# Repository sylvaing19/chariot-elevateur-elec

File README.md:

# chariot-elevateur-elec
Robot's motherboard Eagle files

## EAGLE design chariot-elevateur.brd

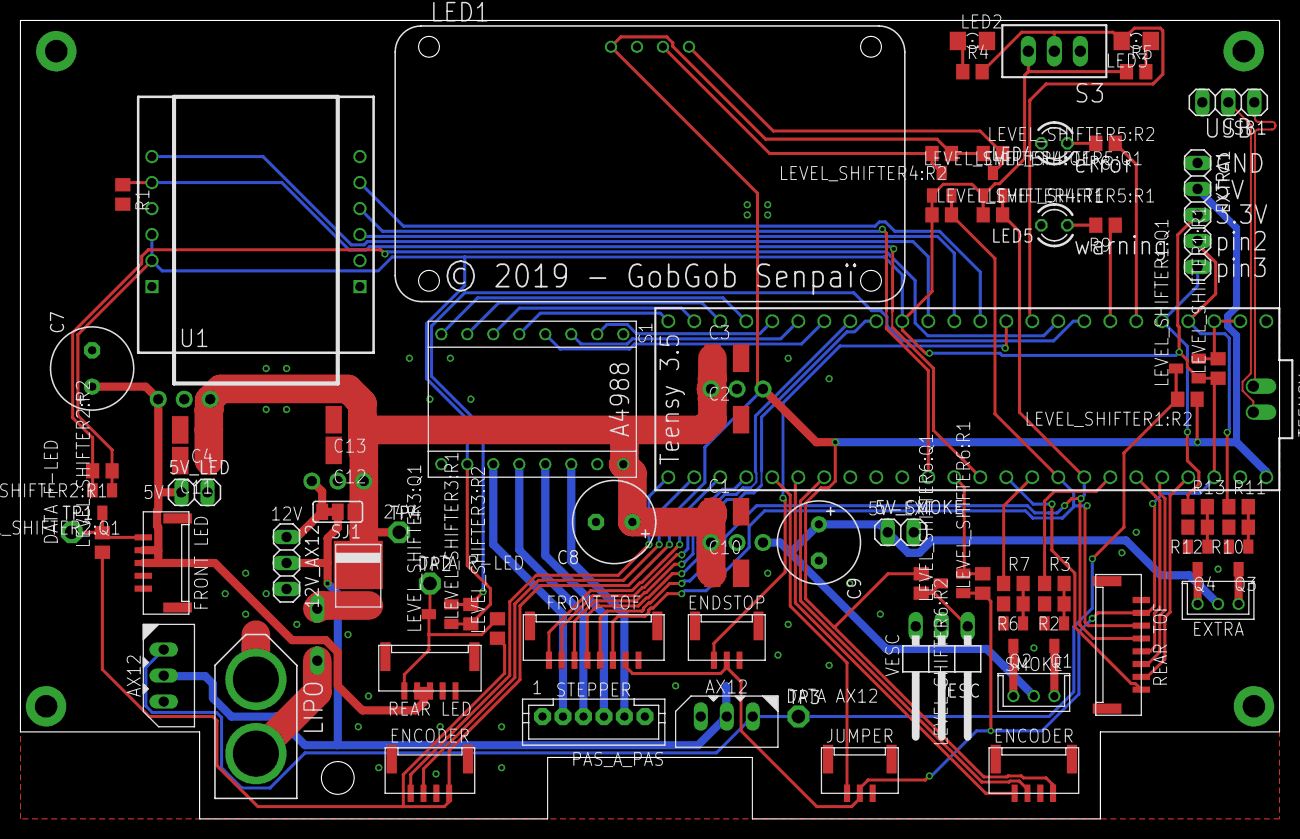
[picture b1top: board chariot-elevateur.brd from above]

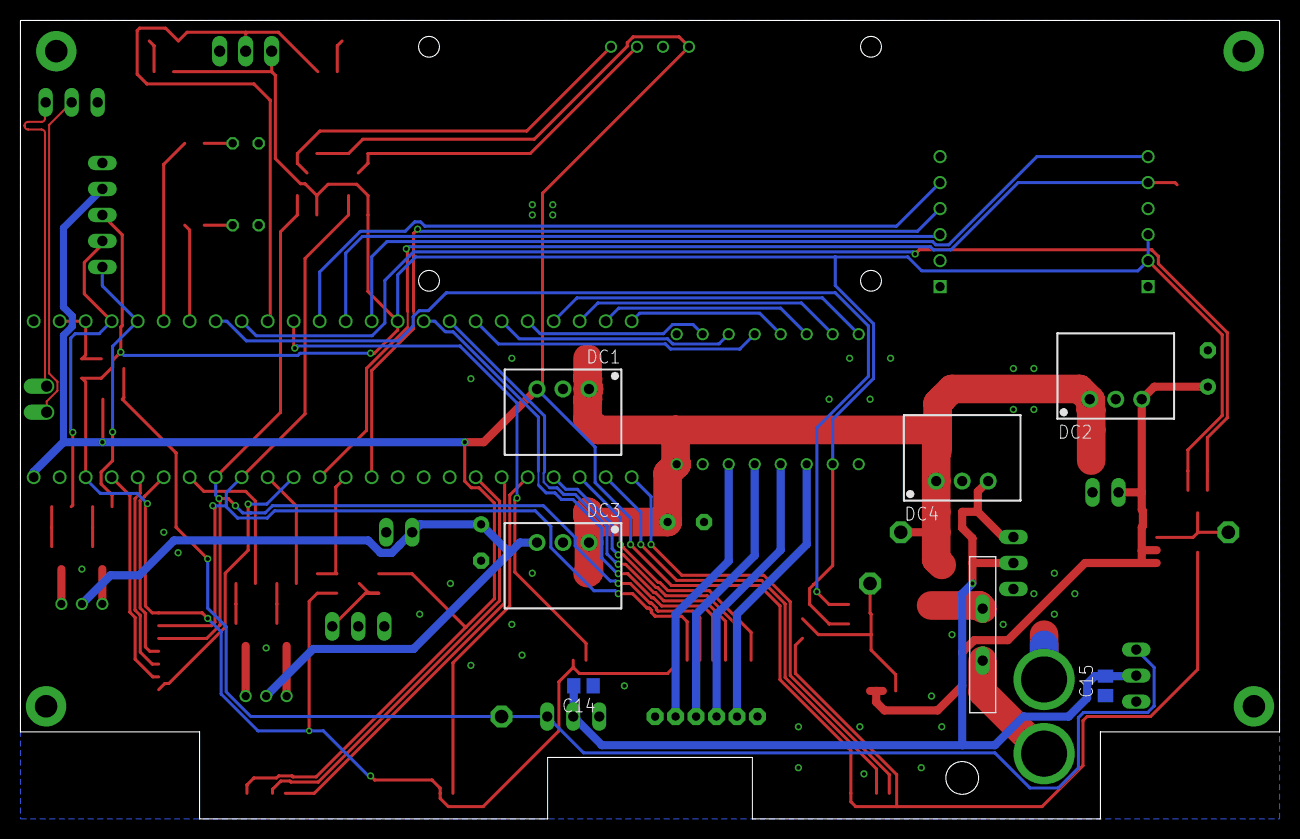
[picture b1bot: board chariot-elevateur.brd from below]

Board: 2 copper layers, 123.0 x 78.0 mm, 88 parts (7 on the bottom side), 73 nets.

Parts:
5V_LED, 5V_SMOKE: 1X02
12V_AX12: 1X03
AX12_AR, AX12_AV: DYNAMIXEL-1X03AX; DYNAMIXEL_AX_1X03
C1, C2, C3, C4, C10, C11, C12, C13: 10µF/50V; C1210
C7, C9: 220µF/25V; E3,5-8
C8: 100µF/50V; E3,5-8
C14, C15: 1µF; C0805
D1: DIODE_S15P45; TO-277A
DC1, DC2: TSR 1-2450; SIP3
DC3: TSR 2-2450; SIP3
DC4: TSR 2-24120; SIP3
ENCODEUR_DROIT: JST-04GH-V; GH-04-V
ENCODEUR_GAUCHE: JST-04GH-V; GH-04-V
ENDSTOP: JST-03; GH-03-V
EXTRA: DYNAMIXEL-1X03XL; DYNAMIXEL_XL_1X03
EXTRA1: 1X05
FUMIGENE: DYNAMIXEL-1X03XL; DYNAMIXEL_XL_1X03
JUMPER: JST-03; GH-03-V
LED1: ADAFRUIT_7-SEGMENT-LED; 0.56"LED_BACKPACK
LED2: blue; 1206
LED3: orange; 1206
LED4: red; LED3MM
LED5: orange; LED3MM
LEVEL_SHIFTER1:Q1, LEVEL_SHIFTER2:Q1, LEVEL_SHIFTER3:Q1, LEVEL_SHIFTER4:Q1, LEVEL_SHIFTER5:Q1, LEVEL_SHIFTER6:Q1: BSS138; SOT23
LEVEL_SHIFTER1:R1, LEVEL_SHIFTER1:R2, LEVEL_SHIFTER2:R1, LEVEL_SHIFTER2:R2, LEVEL_SHIFTER3:R1, LEVEL_SHIFTER3:R2, LEVEL_SHIFTER4:R1, LEVEL_SHIFTER4:R2, LEVEL_SHIFTER5:R1, LEVEL_SHIFTER5:R2, LEVEL_SHIFTER6:R1, LEVEL_SHIFTER6:R2: 10k; R0805
LIPO: XT-60
P1: RG500; 5MM
PAS_A_PAS: JST-PH6
PHARES_AR: JST-05; GH-05-V
PHARES_AV: JST-05; GH-05-V
Q1, Q2, Q3, Q4: DMN2056U; SOT23
R1, R2, R6, R10, R12: 10k; R0805
R3, R7, R11, R13: 100; R0805
R4, R5, R8, R9: 330; R0805
S1: A4988-BREAKOUT
S3: TL36PO; TL3XPO
SJ1: SJ_2
TEENSY: TEENSY_3.5_DIL+USB
TOF_AR: JST-08; GH-08-V
TOF_AV: JST-08; GH-08-V
TP1, TP2, TP3, TP4: PTR1PAD1-13; P1-13
U1: WIZ820IO; WIZ820
USB1: 1X03
VESC: 1X03/90

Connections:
+3V3: ENDSTOP.2, EXTRA1.3, JUMPER.2, LEVEL_SHIFTER1:Q1.1, LEVEL_SHIFTER1:R1.1, LEVEL_SHIFTER2:Q1.1, LEVEL_SHIFTER2:R1.1, LEVEL_SHIFTER3:Q1.1, LEVEL_SHIFTER3:R1.1, LEVEL_SHIFTER4:Q1.1, LEVEL_SHIFTER4:R1.1, LEVEL_SHIFTER5:Q1.1, LEVEL_SHIFTER5:R1.1, LEVEL_SHIFTER6:Q1.1, LEVEL_SHIFTER6:R1.1, R5.1, S1.VDD, S3.3, TEENSY.3.3V, TEENSY.3.3V3, TOF_AR.2, TOF_AV.2, U1.VIN1, U1.VIN2
+5V/1: DC1.3, ENCODEUR_DROIT.1, ENCODEUR_GAUCHE.1, EXTRA1.2, LED1.VCC, LEVEL_SHIFTER1:R2.1, LEVEL_SHIFTER2:R2.1, LEVEL_SHIFTER3:R2.1, LEVEL_SHIFTER4:R2.1, LEVEL_SHIFTER5:R2.1, LEVEL_SHIFTER6:R2.1, TEENSY.VIN
+5V/2: 5V_LED.1, C7.+, DC2.3, PHARES_AR.3, PHARES_AR.4, PHARES_AV.3, PHARES_AV.4
+5V/3: 5V_SMOKE.1, C9.+, DC3.3, EXTRA.VCC, FUMIGENE.VCC
+12V: 12V_AX12.2, AX12_AR.DYN_VCC, AX12_AV.DYN_VCC, C14.2, C15.2, SJ1.2
+24V: C1.1, C2.1, C3.1, C4.1, C8.+, C10.1, C11.1, C12.1, C13.1, D1.-, DC1.1, DC2.1, DC3.1, DC4.1, S1.VMOT, SJ1.1, TP4.TP
CHOOSE_COLOR: LED3.C, R4.2, S3.2, TEENSY.8
CMD_DEL_AR: LEVEL_SHIFTER3:Q1.2, LEVEL_SHIFTER3:R1.2, TEENSY.6
CMD_DEL_AR_5V: LEVEL_SHIFTER3:Q1.3, LEVEL_SHIFTER3:R2.2, PHARES_AR.5, TP2.TP
CMD_DEL_AV: LEVEL_SHIFTER2:Q1.2, LEVEL_SHIFTER2:R1.2, TEENSY.7
CMD_DEL_AV_5V: LEVEL_SHIFTER2:Q1.3, LEVEL_SHIFTER2:R2.2, PHARES_AV.5, TP1.TP
CMD_FUM_POMPE: R3.1, TEENSY.20/A6
CMD_FUM_RES: R7.1, TEENSY.17/A3
DEL_ERROR: R8.1, TEENSY.4
DEL_WARNING: R9.1, TEENSY.5
DIR: S1.DIR, TEENSY.29
ENC_D_A: ENCODEUR_DROIT.3, TEENSY.39/A20
ENC_D_B: ENCODEUR_DROIT.4, TEENSY.38/A19
ENC_G_A: ENCODEUR_GAUCHE.3, TEENSY.34/A15
ENC_G_B: ENCODEUR_GAUCHE.4, TEENSY.33/A14
ENDSTOP: ENDSTOP.3, TEENSY.9
ETH_MISO: TEENSY.12, U1.MISO
ETH_MOSI: TEENSY.11, U1.MOSI
ETH_RST: R1.1, TEENSY.15/A1, U1.RESET
ETH_SCLK: TEENSY.13, U1.SCLK
ETH_SS: TEENSY.10, U1.SS
EXTRA_GPIO_1: EXTRA1.4, R11.1, TEENSY.2
EXTRA_GPIO_2: EXTRA1.5, R13.1, TEENSY.3
EXTRA_POWER_SWITCH_1: EXTRA.GND, Q3.3
EXTRA_POWER_SWITCH_2: EXTRA.DATA, Q4.3
FUM_POMPE: FUMIGENE.GND, Q1.3
FUM_RES: FUMIGENE.DATA, Q2.3
GND: 5V_LED.2, 5V_SMOKE.2, 12V_AX12.3, AX12_AR.GND, AX12_AV.GND, C1.2, C2.2, C3.2, C4.2, C7.-, C8.-, C9.-, C10.2, C11.2, C12.2, C13.2, C14.1, C15.1, DC1.2, DC2.2, DC3.2, DC4.2, ENCODEUR_DROIT.2, ENCODEUR_GAUCHE.2, ENDSTOP.1, EXTRA1.1, JUMPER.1, LED1.GND, LED2.C, LED4.K, LED5.K, LIPO.(-), PHARES_AR.1, PHARES_AR.2, PHARES_AV.1, PHARES_AV.2, Q1.2, Q2.2, Q3.2, Q4.2, R1.2, R2.2, R6.2, R10.2, R12.2, S1.GND1, S1.GND2, S3.1, TEENSY.AGND, TEENSY.GND, TEENSY.GND1, TOF_AR.1, TOF_AV.1, U1.GND1, U1.GND2, U1.GND3, U1.PWDN, USB1.3, VESC.3
JUMPER: JUMPER.3, TEENSY.37/A18
unnamed: LED4.A, R8.2
unnamed: PAS_A_PAS.2, S1.1B
unnamed: PAS_A_PAS.3, S1.1A
unnamed: D1.+1, D1.+2, P1.P$1
unnamed: PAS_A_PAS.4, S1.2A
unnamed: PAS_A_PAS.5, S1.2B
unnamed: LED2.A, R4.1
unnamed: LED3.A, R5.2
unnamed: Q3.1, R10.1, R11.2
unnamed: Q1.1, R2.1, R3.2
unnamed: LED5.A, R9.2
unnamed: Q4.1, R12.1, R13.2
unnamed: Q2.1, R6.1, R7.2
REG_12V: 12V_AX12.1, DC4.3, SJ1.3
SCL: LEVEL_SHIFTER5:Q1.2, LEVEL_SHIFTER5:R1.2, TEENSY.19/A5, TOF_AR.4, TOF_AV.4
SCL_5V: LED1.SCL, LEVEL_SHIFTER5:Q1.3, LEVEL_SHIFTER5:R2.2
SDA: LEVEL_SHIFTER4:Q1.2, LEVEL_SHIFTER4:R1.2, TEENSY.18/A4, TOF_AR.3, TOF_AV.3
SDA_5V: LED1.SDA, LEVEL_SHIFTER4:Q1.3, LEVEL_SHIFTER4:R2.2
SERIAL_AX12: LEVEL_SHIFTER1:Q1.2, LEVEL_SHIFTER1:R1.2, TEENSY.0, TEENSY.1
SERIAL_AX12_5V: AX12_AR.DATA, AX12_AV.DATA, LEVEL_SHIFTER1:Q1.3, LEVEL_SHIFTER1:R2.2, TP3.TP
STEP: S1.STEP, TEENSY.30
S_MS1: S1.MS1, TEENSY.28
S_MS2: S1.MS2, TEENSY.27
S_MS3: S1.MS3, TEENSY.26
S_N_RST: S1.N_RST, TEENSY.32/A13
S_N_SLEEP: S1.N_SLEEP, TEENSY.31/A12
TOF_AR_D: TEENSY.23/A9, TOF_AR.7
TOF_AR_FD: TEENSY.16/A2, TOF_AR.8
TOF_AR_FG: TEENSY.21/A7, TOF_AR.5
TOF_AR_G: TEENSY.22/A8, TOF_AR.6
TOF_AV_D: TEENSY.35/A16, TOF_AV.8
TOF_AV_G: TEENSY.24, TOF_AV.5
TOF_AV_SD: TEENSY.36/A17, TOF_AV.7
TOF_AV_SG: TEENSY.25, TOF_AV.6
USB_D+: TEENSY.USBD+, USB1.1
USB_D-: TEENSY.USBD-, USB1.2
VESC_CMD: LEVEL_SHIFTER6:Q1.2, LEVEL_SHIFTER6:R1.2, TEENSY.14/A0
VESC_CMD_5V: LEVEL_SHIFTER6:Q1.3, LEVEL_SHIFTER6:R2.2, VESC.1
V_LIPO: LIPO.(+), P1.P$2

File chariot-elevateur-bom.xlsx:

Qty | Value | Device | Package | Parts | Description | RS | RS_F | ADAFRUIT | ORDER
1 |  | JST-PH6 | JST-PH6 | PAS_A_PAS |  | 820-1447 | 820-1481 |  | NO
2 | 100 | R-EU_R0805 | R0805 | R3, R7 | RESISTOR, European symbol |  |  |  | NO
1 | 100µF/50V | CPOL-EUE3.5-8 | E3,5-8 | C8 | POLARIZED CAPACITOR, European symbol |  |  |  | NO
13 | 10k | R-EU_R0805 | R0805 | LEVEL_SHIFTER1:R1, LEVEL_SHIFTER1:R2, LEVEL_SHIFTER2:R1, LEVEL_SHIFTER2:R2, LEV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 | RESISTOR, European symbol |  |  |  | NO
8 | 10µF/50V | C-EUC1210 | C1210 | C1, C2, C3, C4, C10, C11, C12, C13 | CAPACITOR, European symbol |  |  |  | YES
2 | 1µF | C-EUC0805 | C0805 | C14, C15 | CAPACITOR, European symbol |  |  |  | NO
2 | 220µF/25V | CPOL-EUE3.5-8 | E3,5-8 | C7, C9 | POLARIZED CAPACITOR, European symbol |  |  |  | NO
4 | 330 | R-EU_R0805 | R0805 | R4, R5, R8, R9 | RESISTOR, European symbol |  |  |  | NO
1 | A4988-BREAKOUT | A4988-BREAKOUT | A4988-BREAKOUT | S1 |  |  |  |  | YES
1 | ADAFRUIT_7-SEGMENT-LED | ADAFRUIT_7-SEGMENT-LED | 0.56LED_BACKPACK" | LED1 |  |  |  | 879 | YES
5 | BSS138 | BSS123 | SOT23 | LEVEL_SHIFTER1:Q1, LEVEL_SHIFTER2:Q1, LEVEL_SHIFTER3:Q1, LEVEL_SHIFTER4:Q1, LEV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 | N-CHANNEL MOS FET | 669-7559 |  |  | NO
1 | DIODE_S15P45 | DIODE_S15P45 | TO-277A | D1 |  | 917-9118 |  |  | NO
2 | DMN2056U | BSS123 | SOT23 | Q1, Q2 | N-CHANNEL MOS FET | 133-3376 |  |  | YES
2 | DYNAMIXEL-1X03AX | DYNAMIXEL-1X03AX | DYNAMIXEL_AX_1X03 | AX12_AR, AX12_AV |  | 687-8124 |  |  | NO
1 | DYNAMIXEL-1X03XL | DYNAMIXEL-1X03XL | DYNAMIXEL_XL_1X03 | FUMIGENE |  | 688-3283 |  |  | YES
2 | JST-03 | JST-03 | GH-03-V | ENDSTOP, JUMPER |  | 752-1765 | 752-1737 |  | YES
2 | JST-04GH-V | JST-04GH-V | GH-04-V | ENCODEUR_DROIT, ENCODEUR_GAUCHE |  | 752-1769 | 752-1731 |  | YES
2 | JST-05 | JST-05 | GH-05-V | PHARES_AR, PHARES_AV |  | 752-1778 | 752-1740 |  | YES
2 | JST-08 | JST-08 | GH-08-V | TOF_AR, TOF_AV |  | 752-1775 | 752-1747 |  | YES
1 | RG500 | RGEF800 | 5MM | P1 |  | 817-1680 |  |  | YES
1 | TL36PO | TL36PO | TL3XPO | S3 | TINY SWITCH ON - ON | 913-9069 |  |  | NO
2 | TSR 1-2450 | R-78C5.0-1.0 | SIP3 | DC1, DC2 | INNOLINE DC/DC-Converter 1.0 AMP SIP3 Single Output | 666-4379 |  |  | YES
1 | TSR 2-24120 | R-78C12-1.0 | SIP3 | DC4 | INNOLINE DC/DC-Converter 1.0 AMP SIP3 Single Output | 906-8493 |  |  | YES
1 | TSR 2-2450 | R-78C5.0-1.0 | SIP3 | DC3 | INNOLINE DC/DC-Converter 1.0 AMP SIP3 Single Output | 906-8487 |  |  | YES
1 | WIZ820IO | WIZ820IO | WIZ820 | U1 |  | 758-1032 |  |  | YES
1 | blue | LEDSMT1206 | 1206 | LED2 | LED | 692-1073 |  |  | NO
1 | orange | LED3MM | LED3MM | LED5 | LED | 127-8387 |  |  | NO
1 | orange | LEDSMT1206 | 1206 | LED3 | LED | 726-9215 |  |  | NO
1 | red | LED3MM | LED3MM | LED4 | LED | 619-4886 |  |  | NO
1 | XT-60 | XT-60 | XT-60 | CON1 |  |  |  |  | YES
20 | JST-GH cable | JST-GH cable | JST-GH cable |  |  | 820-1393 |  |  | YES

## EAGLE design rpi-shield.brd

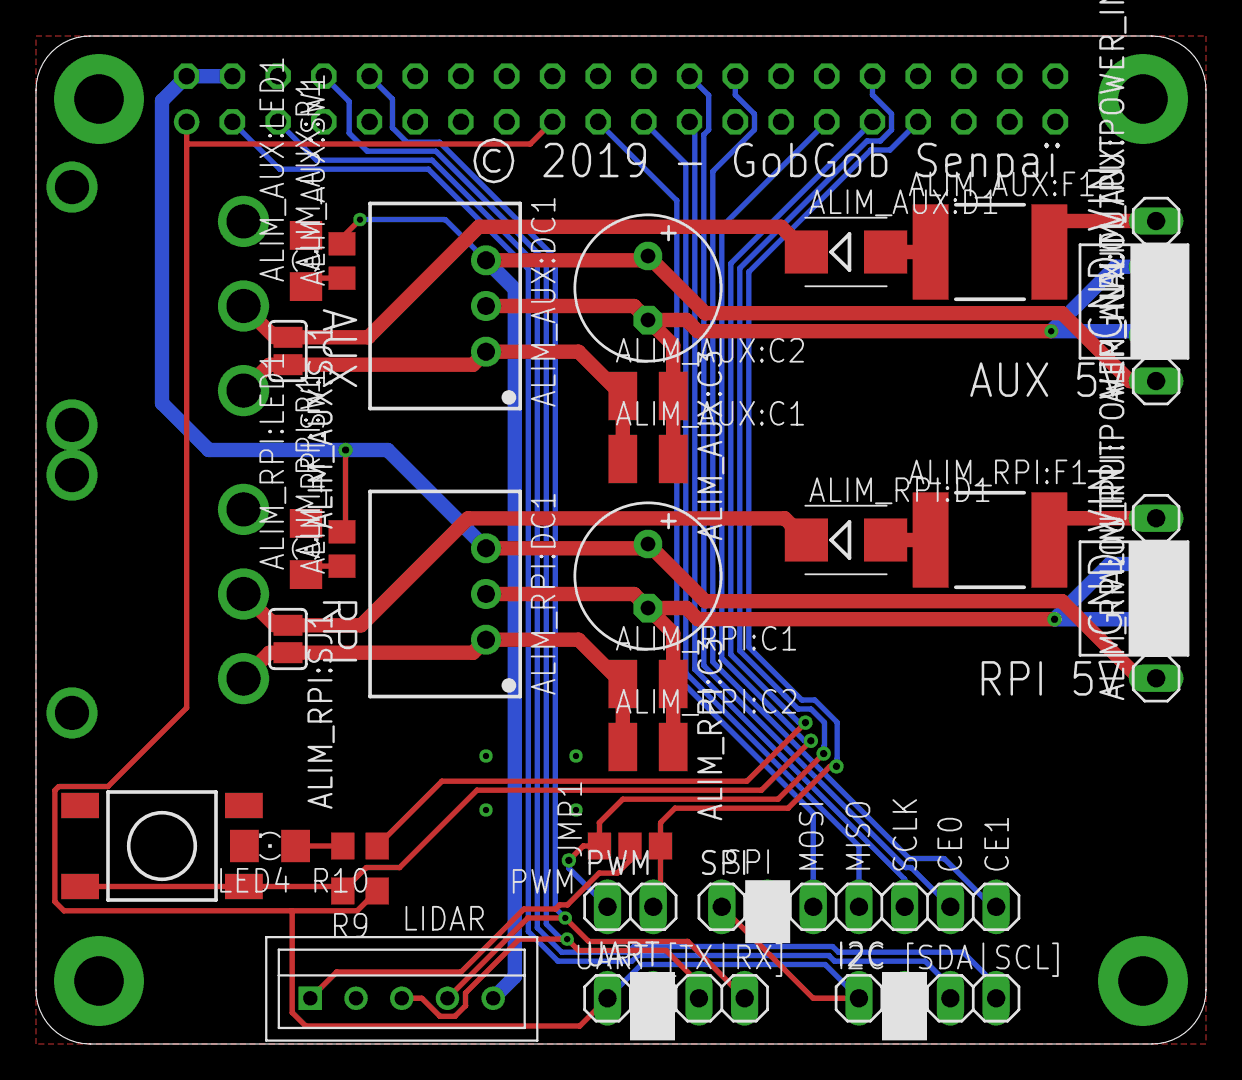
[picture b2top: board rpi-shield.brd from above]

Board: 2 copper layers, 65.0 x 56.0 mm, 35 parts (1 on the bottom side), 29 nets.

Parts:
ALIM_AUX:C1, ALIM_AUX:C2: 10µF/50V; C1210
ALIM_AUX:C3: 220µF/25V; E3,5-8
ALIM_AUX:D1: SS56B; SMB
ALIM_AUX:DC1: TSR 2-2450; SIP3
ALIM_AUX:F1: MF-LSMF300
ALIM_AUX:LED1: blue; 1206
ALIM_AUX:OUTPUT: 1X02
ALIM_AUX:POWER_INPUT: 1X02
ALIM_AUX:R1: 470; R0805
ALIM_AUX:SJ1: SJ
ALIM_AUX:SW1: 5MS1S102AM6QES; SPDT_SLIDE_SWITCH
ALIM_RPI:C1, ALIM_RPI:C2: 10µF/50V; C1210
ALIM_RPI:C3: 220µF/25V; E3,5-8
ALIM_RPI:D1: SS56B; SMB
ALIM_RPI:DC1: TSR 2-2450; SIP3
ALIM_RPI:F1: MF-LSMF300
ALIM_RPI:LED1: blue; 1206
ALIM_RPI:OUTPUT: 1X02
ALIM_RPI:POWER_INPUT: 1X02
ALIM_RPI:R1: 470; R0805
ALIM_RPI:SJ1: SJ
ALIM_RPI:SW1: 5MS1S102AM6QES; SPDT_SLIDE_SWITCH
I2C: 1X04
JMP1: 0R-JUMPA; A0R-JMP
LED4: red; 1206
LIDAR: 05-JST-B5B-XH-A; B5B-XH
PWM: 1X02
R9: 10k; R0805
R10: 330; R0805
SPI: 1X07
SV1: FE20-2
U$2: PUSH-BUTTON
UART: 1X04

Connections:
+3V3: I2C.1, R9.1, SPI.1, SV1.1, SV1.17, UART.1
+5V: ALIM_RPI:C3.+, ALIM_RPI:DC1.3, ALIM_RPI:OUTPUT.1, ALIM_RPI:R1.2, SV1.2, SV1.4
+5V/1: ALIM_AUX:C3.+, ALIM_AUX:DC1.3, ALIM_AUX:OUTPUT.1, ALIM_AUX:R1.2, LIDAR.P$5
ALIM_AUX:N$1: ALIM_AUX:C1.1, ALIM_AUX:C2.1, ALIM_AUX:DC1.1, ALIM_AUX:SJ1.2, ALIM_AUX:SW1.1
ALIM_AUX:N$3: ALIM_AUX:LED1.A, ALIM_AUX:R1.1
ALIM_AUX:N$4: ALIM_AUX:D1.C, ALIM_AUX:SJ1.1, ALIM_AUX:SW1.C
ALIM_AUX:N$6: ALIM_AUX:D1.A, ALIM_AUX:F1.1
ALIM_AUX:N$7: ALIM_AUX:F1.2, ALIM_AUX:POWER_INPUT.2
ALIM_RPI:N$1: ALIM_RPI:C1.1, ALIM_RPI:C2.1, ALIM_RPI:DC1.1, ALIM_RPI:SJ1.2, ALIM_RPI:SW1.1
ALIM_RPI:N$3: ALIM_RPI:LED1.A, ALIM_RPI:R1.1
ALIM_RPI:N$4: ALIM_RPI:D1.C, ALIM_RPI:SJ1.1, ALIM_RPI:SW1.C
ALIM_RPI:N$6: ALIM_RPI:D1.A, ALIM_RPI:F1.1
ALIM_RPI:N$7: ALIM_RPI:F1.2, ALIM_RPI:POWER_INPUT.2
CE0: SPI.6, SV1.24
CE1: SPI.7, SV1.26
GND: ALIM_AUX:C1.2, ALIM_AUX:C2.2, ALIM_AUX:C3.-, ALIM_AUX:DC1.2, ALIM_AUX:LED1.C, ALIM_AUX:OUTPUT.2, ALIM_AUX:POWER_INPUT.1, ALIM_AUX:SW1.P$4, ALIM_AUX:SW1.P$5, ALIM_RPI:C1.2, ALIM_RPI:C2.2, ALIM_RPI:C3.-, ALIM_RPI:DC1.2, ALIM_RPI:LED1.C, ALIM_RPI:OUTPUT.2, ALIM_RPI:POWER_INPUT.1, ALIM_RPI:SW1.P$4, ALIM_RPI:SW1.P$5, I2C.2, LED4.C, LIDAR.P$2, SPI.2, SV1.6, SV1.9, SV1.14, SV1.20, SV1.25, SV1.30, SV1.34, SV1.39, U$2.1, U$2.2, UART.2
MISO: SPI.4, SV1.21
MOSI: SPI.3, SV1.19
unnamed: JMP1.2, LIDAR.P$1
unnamed: R9.2, SV1.29, U$2.3, U$2.4
unnamed: R10.1, SV1.31
unnamed: LED4.A, R10.2
PWM0: JMP1.1, PWM.1, SV1.32
PWM1: JMP1.3, PWM.2, SV1.33
RX: LIDAR.P$4, SV1.10, UART.4
SCL: I2C.4, SV1.5
SCLK: SPI.5, SV1.23
SDA: I2C.3, SV1.3
TX: LIDAR.P$3, SV1.8, UART.3

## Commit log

2018-12-17 Board dimensions
2018-12-17 Placement des gros composants
2018-12-17 end-of-day-commit
2018-12-18 more components
2018-12-19 Add power connector
2018-12-19 placement connecteurs
2018-12-28 end-of-the-day commit
2018-12-28 end-of-day commit
2018-12-31 Update components ref + add debug LEDs + map unused pins for debug
2018-12-31 add BOM
2019-01-07 new file for rpi shield
2019-01-08 shield raspi: shematics done
2019-01-08 rename rpi shield file
2019-01-09 placement composants rpi-shield
2019-01-10 add debug features
2019-01-11 all done, missing doc
2019-01-11 CAM files are ready
2019-01-11 FAB version
2019-01-12 maj BOM
2019-01-20 push eagle boards to fusion

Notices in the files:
chariot-elevateur.brd:
© 2019 - GobGob Senpaï
